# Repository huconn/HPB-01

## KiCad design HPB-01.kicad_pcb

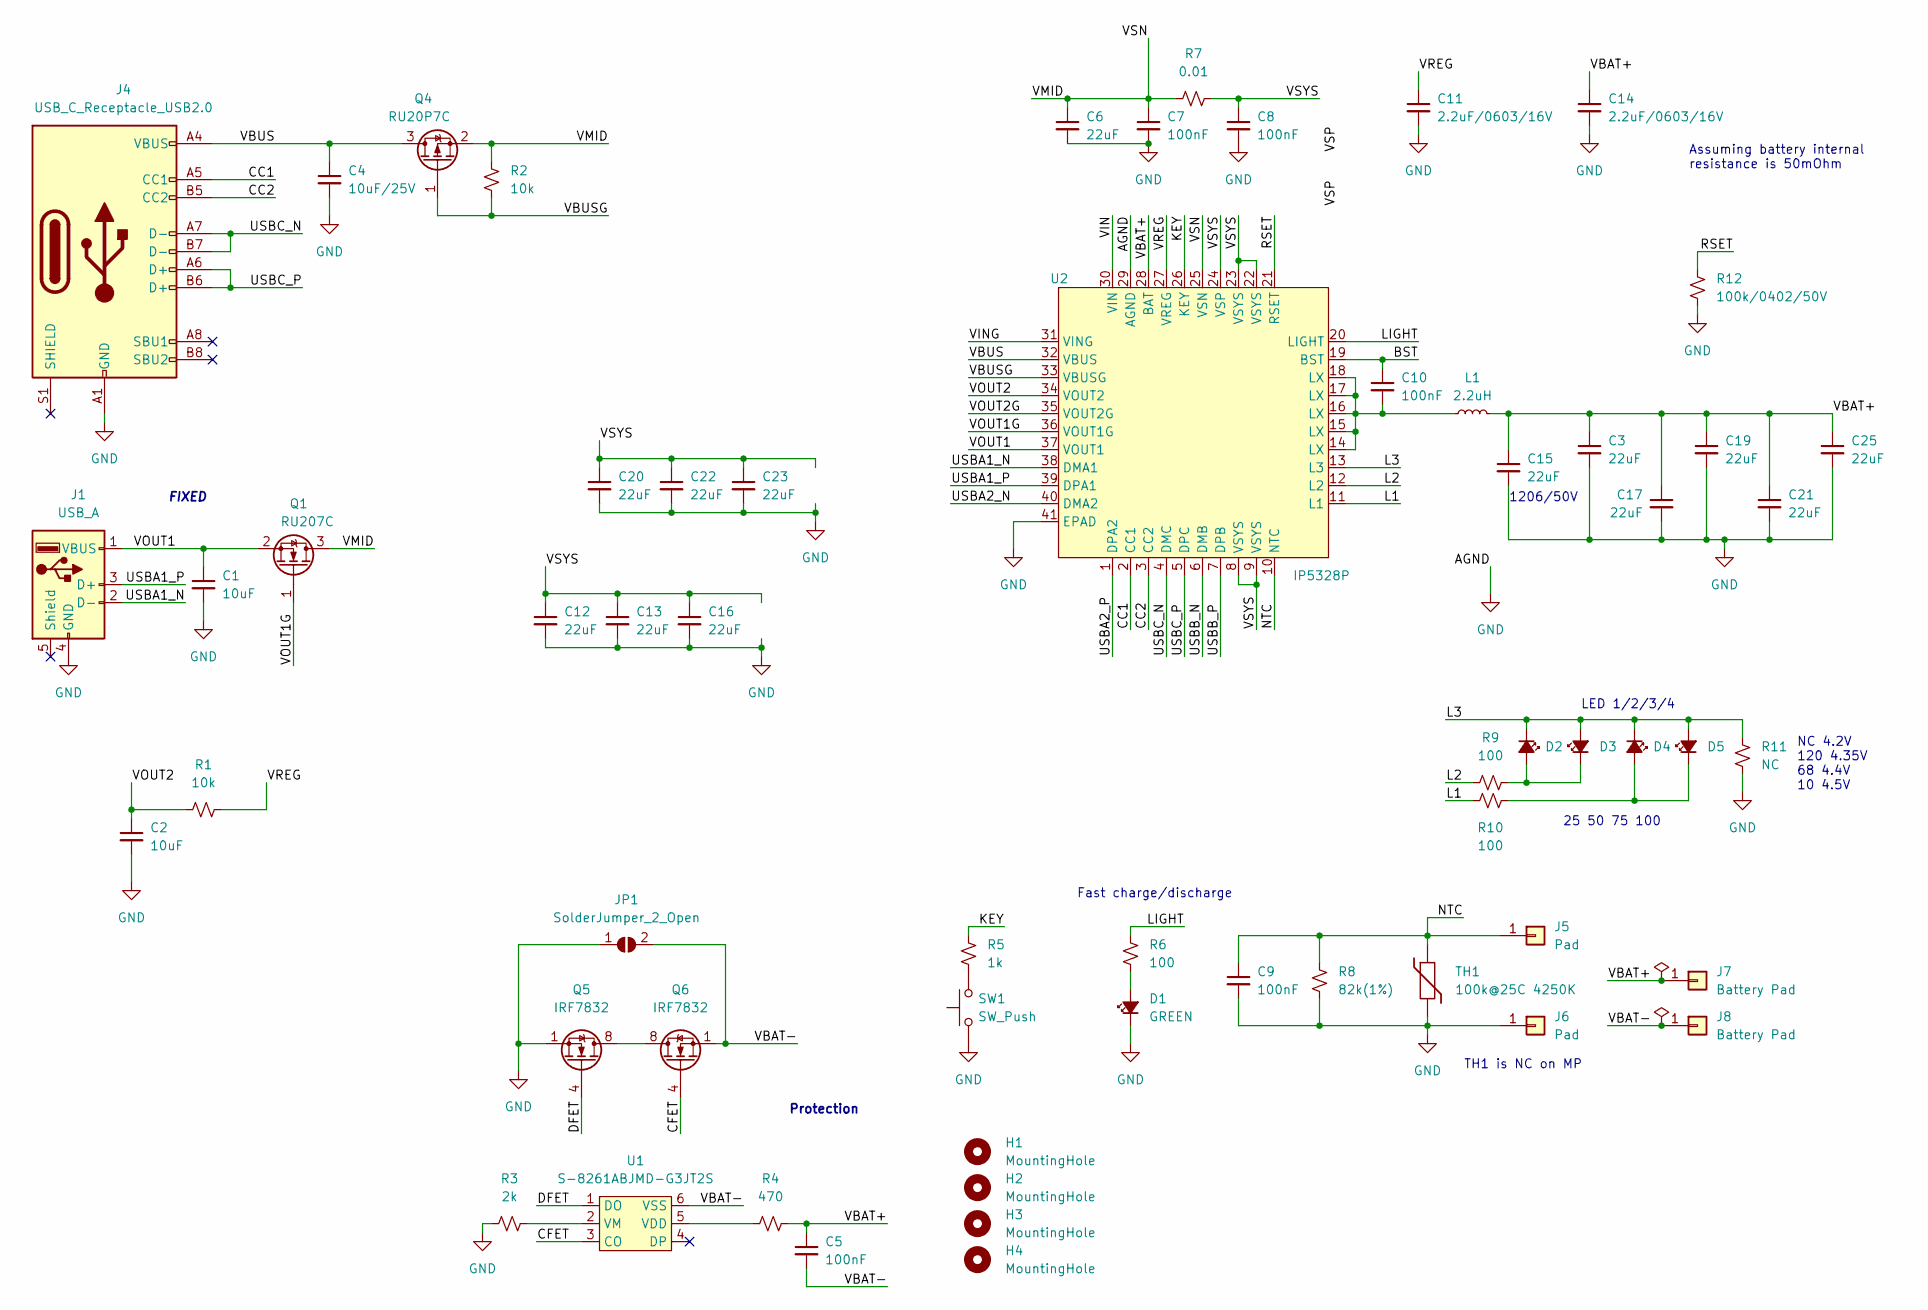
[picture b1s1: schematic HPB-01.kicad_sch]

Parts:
C1, C2: 10uF; C_0603_1608Metric; LCSC C96446
C3, C6, C12, C13, C15, C16, C17, C19, C20, C21, C22, C23, C25: 22uF; C_0805_2012Metric; LCSC C45783
C4: 10uF/25V; C_0603_1608Metric; LCSC C96446
C5, C7, C8, C9, C10: 100nF; C_0603_1608Metric; LCSC C14663
C11, C14: 2.2uF/0603/16V; C_0603_1608Metric; LCSC C23630
D1: GREEN; LED_0603_1608Metric; LCSC C72043
D2, D3, D4, D5: BLUE; LED_0603_1608Metric; LCSC C72041
H1, H2, H3, H4: MountingHole; MountingHole_2.2mm_M2
J1: USB_A; USB_A_FEMALE_905-662A203S10200; LCSC C41014
J4: USB_C_Receptacle_USB2.0; USB_C_Receptacle_HRO_TYPE-C-31-M-12; LCSC C165948
J5, J6: Pad; TestPoint_Pad_D1.5mm
J7, J8: Battery Pad
JP1: SolderJumper_2_Open; SolderJumper-2_P1.3mm_Open_Pad1.0x1.5mm
L1: 2.2uH; L_Wuerth_HCI-1050; LCSC C149538
Q1: RU207C; SOT-23; LCSC C515680
Q4: RU20P7C; SOT-23; LCSC C181984
Q5, Q6: IRF7832; SOIC-8_3.9x4.9mm_P1.27mm; LCSC C3002
R1, R2: 10k; R_0603_1608Metric; LCSC C25804
R3: 2k; R_0603_1608Metric; LCSC C22975
R4: 470; R_0603_1608Metric; LCSC C23179
R5: 1k; R_0603_1608Metric; LCSC C21190
R6, R9, R10: 100; R_0603_1608Metric; LCSC C22775
R7: 0.01; R_1206_3216Metric; LCSC C309628
R8: 82k(1%); R_0603_1608Metric; LCSC C23254
R11: NC; R_0603_1608Metric
R12: 100k/0402/50V; R_0402_1005Metric; LCSC C25086
SW1: SW_Push; SW_Push_1P1T-MP_NO_Horizontal_Alps_SKRTLAE010; LCSC C127481
TH1: 100k@25C 4250K; R_0603_1608Metric; LCSC C92368
U1: S-8261ABJMD-G3JT2S; SOT-23-6; LCSC C28081
U2: IP5328P; QFN-40-1EP_6x6mm_P0.5mm_EP4.6x4.6mm; LCSC C188809

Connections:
/BST: C10.1, U2.19 (BST)
/CC1: J4.A5 (CC1), U2.2 (CC1)
/CC2: J4.B5 (CC2), U2.3 (CC2)
/CFET: Q6.4 (G), U1.3 (CO)
/DFET: Q5.4 (G), U1.1 (DO)
/KEY: R5.1, U2.26 (KEY)
/L1: R10.1, U2.11 (L1)
/L2: R9.1, U2.12 (L2)
/L3: D2.1 (K), D3.2 (A), D4.1 (K), D5.2 (A), R11.1, U2.13 (L3)
/LIGHT: R6.1, U2.20 (LIGHT)
/NTC: C9.1, J5.1, R8.1, TH1.1, U2.10 (NTC)
/RSET: R12.1, U2.21 (RSET)
/USBA1_N: J1.2 (D-), U2.38 (DMA1)
/USBA1_P: J1.3 (D+), U2.39 (DPA1)
/USBA2_N: U2.40 (DMA2)
/USBA2_P: U2.1 (DPA2)
/USBB_N: U2.6 (DMB)
/USBB_P: U2.7 (DPB)
/USBC_N: J4.A7 (D-), J4.B7 (D-), U2.4 (DMC)
/USBC_P: J4.A6 (D+), J4.B6 (D+), U2.5 (DPC)
/VBAT+: C3.1, C5.1, C14.1, C15.1, C17.1, C19.1, C21.1, C25.1, J7.1, L1.2, R4.2, U2.28 (BAT)
/VBAT-: C5.2, J8.1, JP1.2 (B), Q6.1 (S), Q6.2 (S), Q6.3 (S), U1.6 (VSS)
/VBUS: C4.1, J4.A4 (VBUS), J4.A9 (VBUS), J4.B4 (VBUS), J4.B9 (VBUS), Q4.3 (D), U2.32 (VBUS)
/VBUSG: Q4.1 (G), R2.2, U2.33 (VBUSG)
/VIN: U2.30 (VIN)
/VING: U2.31 (VING)
/VMID: C6.1, C7.1, Q1.3 (D), Q4.2 (S), R2.1, R7.1, U2.25 (VSN)
/VOUT1: C1.1, J1.1 (VBUS), Q1.2 (S), U2.37 (VOUT1)
/VOUT1G: Q1.1 (G), U2.36 (VOUT1G)
/VOUT2: C2.1, R1.1, U2.34 (VOUT2)
/VOUT2G: U2.35 (VOUT2G)
/VREG: C11.1, R1.2, U2.27 (VREG)
/VSYS: C8.1, C12.1, C13.1, C16.1, C20.1, C22.1, C23.1, R7.2, U2.8 (VSYS), U2.9 (VSYS), U2.22 (VSYS), U2.23 (VSYS), U2.24 (VSP)
GND: C1.2, C2.2, C3.2, C4.2, C6.2, C7.2, C8.2, C9.2, C11.2, C12.2, C13.2, C14.2, C15.2, C16.2, C17.2, C19.2, C20.2, C21.2, C22.2, C23.2, C25.2, D1.1 (K), J1.4 (GND), J4.A1 (GND), J4.A12 (GND), J4.B1 (GND), J4.B12 (GND), J6.1, JP1.1 (A), Q5.1 (S), Q5.2 (S), Q5.3 (S), R3.1, R8.2, R11.2, R12.2, SW1.1, TH1.2, U2.29 (AGND), U2.41 (EPAD)
unnamed: C10.2, L1.1, U2.14 (LX), U2.15 (LX), U2.16 (LX), U2.17 (LX), U2.18 (LX)
unnamed: D1.2 (A), R6.2
unnamed: D2.2 (A), D3.1 (K), R9.2
unnamed: D4.2 (A), D5.1 (K), R10.2
unnamed: Q5.5 (D), Q5.6 (D), Q5.7 (D), Q5.8 (D), Q6.5 (D), Q6.6 (D), Q6.7 (D), Q6.8 (D)
unnamed: R3.2, U1.2 (VM)
unnamed: R4.1, U1.5 (VDD)
unnamed: R5.2, SW1.2

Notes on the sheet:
FIXED
LED 1/2/3/4
Protection
TH1 is NC on MP
Fast charge/discharge
25 50 75 100
1206/50V
Assuming battery internal resistance is 50mOhm
NC 4.2V 120 4.35V 68 4.4V 10 4.5V

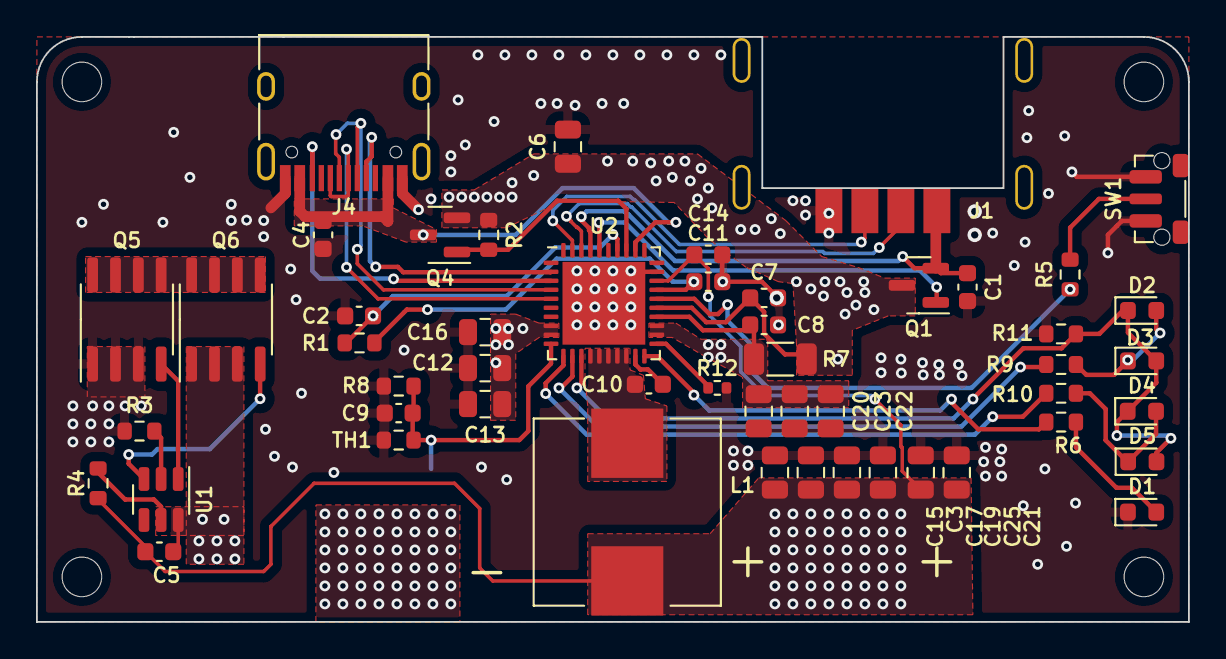
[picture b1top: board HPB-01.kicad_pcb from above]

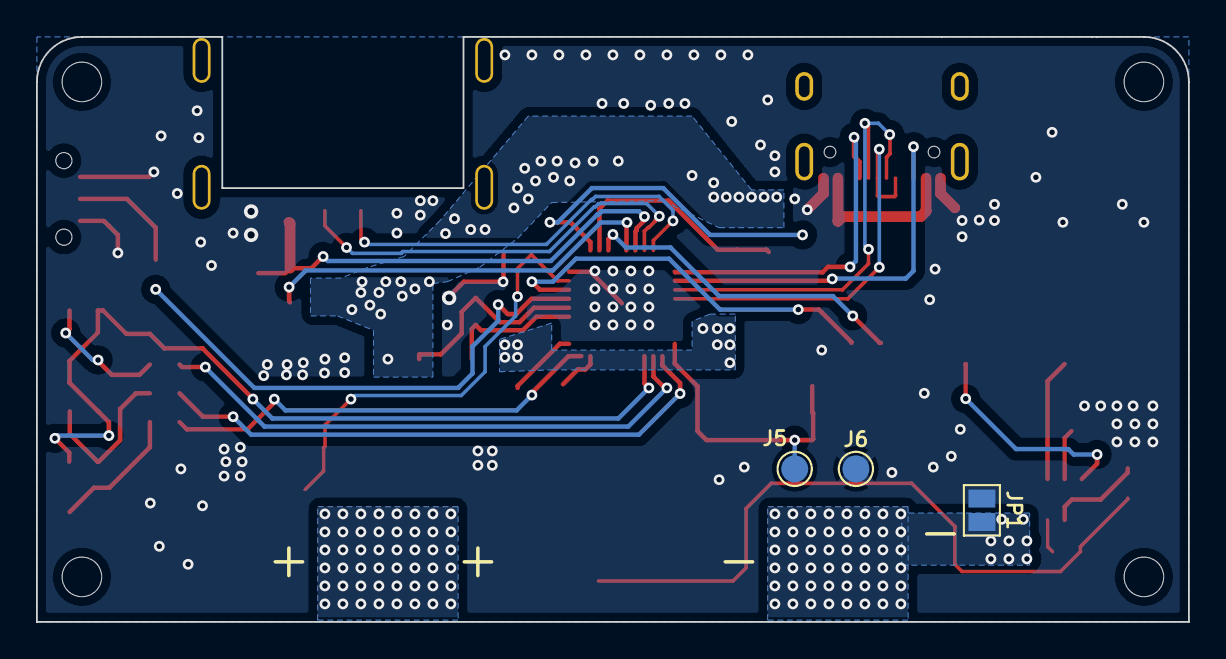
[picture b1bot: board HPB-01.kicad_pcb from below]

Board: 4 copper layers, 64.0 x 32.5 mm, 58 parts (3 on the bottom side), 35 nets.

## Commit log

2021-09-30 ERC and DRC correction
2022-01-17 Change the layout (bigger)
2022-01-18 [WIP] positioning parts on new layout (90%)
2022-01-18 Add some comment for MP
    Add 3D part archive
2022-01-23 PCB artwork complete
2022-01-23 update library and 3d model
2022-02-14 WIP: bug fix and make some improvement
2022-02-15 revision 1.1
